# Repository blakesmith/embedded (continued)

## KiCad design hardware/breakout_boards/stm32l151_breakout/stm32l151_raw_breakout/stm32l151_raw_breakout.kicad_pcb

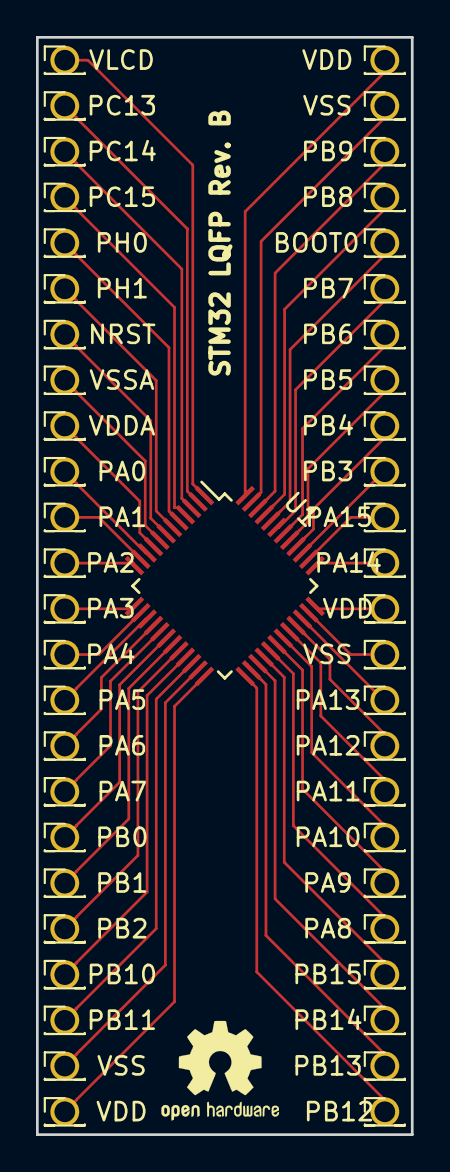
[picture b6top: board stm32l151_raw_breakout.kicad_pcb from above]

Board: 2 copper layers, 20.8 x 61.0 mm, 49 parts (0 on the bottom side), 48 nets.

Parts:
BOOT0: Conn_01x01; Pin_Header_Straight_1x01_Pitch1.27mm
NRST: Conn_01x01; Pin_Header_Straight_1x01_Pitch1.27mm
PA0, PA1, PA2, PA3, PA4, PA5, PA6, PA7, PA8, PA9, PA10, PA11, PA12, PA13, PA14, PA15: Conn_01x01; Pin_Header_Straight_1x01_Pitch1.27mm
PB0, PB1, PB2, PB3, PB4, PB5, PB6, PB7, PB8, PB9, PB10, PB11, PB12, PB13, PB14, PB15: Conn_01x01; Pin_Header_Straight_1x01_Pitch1.27mm
PC13, PC14, PC15: Conn_01x01; Pin_Header_Straight_1x01_Pitch1.27mm
PH0, PH1: Conn_01x01; Pin_Header_Straight_1x01_Pitch1.27mm
U1: STM32L151CCTx; LQFP-48_7x7mm_Pitch0.5mm
VDD: Conn_01x01; Pin_Header_Straight_1x01_Pitch1.27mm
VDD#2, VDD#3: Conn_01x01; Pin_Header_Straight_1x01_Pitch1.27mm
VDDA: Conn_01x01; Pin_Header_Straight_1x01_Pitch1.27mm
VLCD: Conn_01x01; Pin_Header_Straight_1x01_Pitch1.27mm
VSS: Conn_01x01; Pin_Header_Straight_1x01_Pitch1.27mm
VSS#2, VSS#3: Conn_01x01; Pin_Header_Straight_1x01_Pitch1.27mm
VSSA: Conn_01x01; Pin_Header_Straight_1x01_Pitch1.27mm

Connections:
unnamed: NRST.1, U1.7
unnamed: BOOT0.1, U1.44
unnamed: U1.1, VLCD.1
unnamed: PH0.1, U1.5
unnamed: PH1.1, U1.6
unnamed: PC13.1, U1.2
unnamed: PC14.1, U1.3
unnamed: PC15.1, U1.4
unnamed: PB0.1, U1.18
unnamed: PB1.1, U1.19
unnamed: PB2.1, U1.20
unnamed: PB3.1, U1.39
unnamed: PB4.1, U1.40
unnamed: PB5.1, U1.41
unnamed: PB6.1, U1.42
unnamed: PB7.1, U1.43
unnamed: PB8.1, U1.45
unnamed: PB9.1, U1.46
unnamed: PB10.1, U1.21
unnamed: PB11.1, U1.22
unnamed: PB12.1, U1.25
unnamed: PB13.1, U1.26
unnamed: PB14.1, U1.27
unnamed: PB15.1, U1.28
unnamed: U1.24, VDD.1
unnamed: U1.23, VSS.1
unnamed: U1.36, VDD#2.1
unnamed: U1.35, VSS#2.1
unnamed: U1.48, VDD#3.1
unnamed: U1.47, VSS#3.1
unnamed: U1.9, VDDA.1
unnamed: U1.8, VSSA.1
unnamed: PA0.1, U1.10
unnamed: PA1.1, U1.11
unnamed: PA2.1, U1.12
unnamed: PA3.1, U1.13
unnamed: PA4.1, U1.14
unnamed: PA5.1, U1.15
unnamed: PA6.1, U1.16
unnamed: PA7.1, U1.17
unnamed: PA8.1, U1.29
unnamed: PA9.1, U1.30
unnamed: PA10.1, U1.31
unnamed: PA11.1, U1.32
unnamed: PA12.1, U1.33
unnamed: PA13.1, U1.34
unnamed: PA14.1, U1.37
unnamed: PA15.1, U1.38

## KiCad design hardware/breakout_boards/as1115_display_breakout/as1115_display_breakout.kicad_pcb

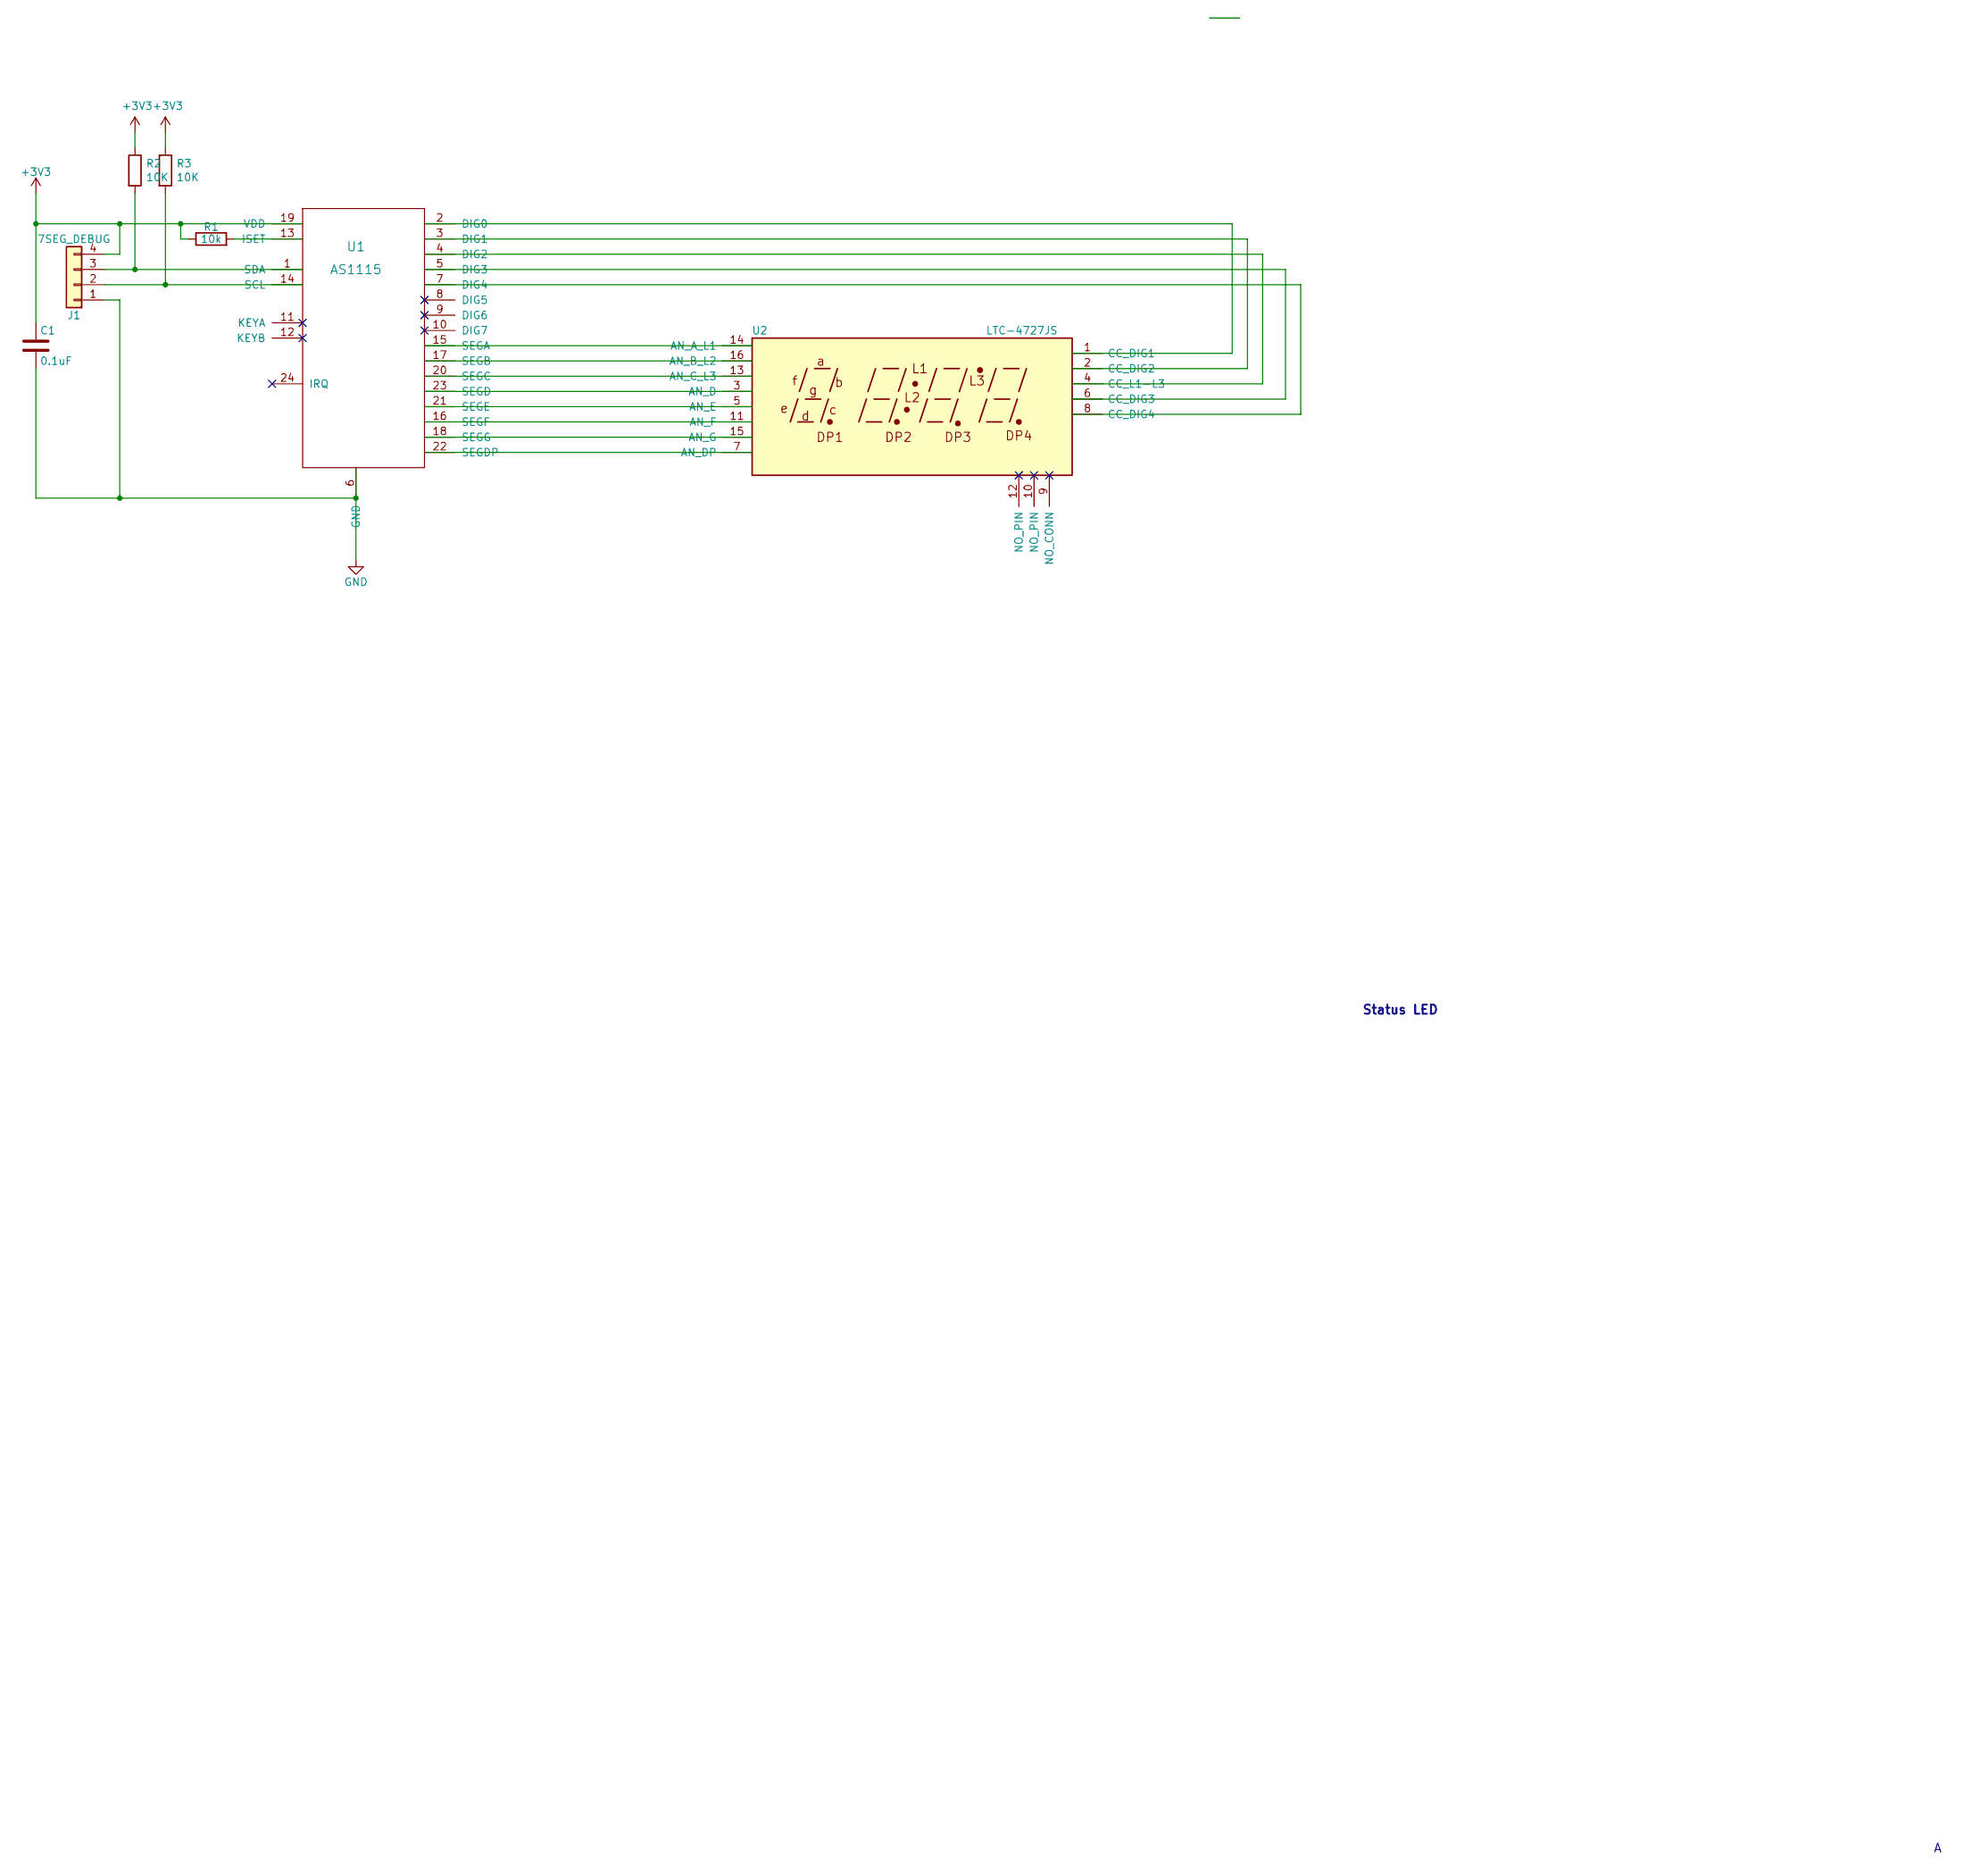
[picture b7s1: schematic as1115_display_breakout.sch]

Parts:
C1: 0.1uF; C_0805_HandSoldering
J1: 7SEG_DEBUG; Pin_Header_Straight_1x04_Pitch2.54mm
R1: 10k; R_0805_HandSoldering
R2, R3: 10K; R_0805_HandSoldering
U1: AS1115; QSOP-24_3.9x8.7mm_Pitch0.635mm
U2: LTC-4727JS; LTC-4727

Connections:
+3V3: C1.1, J1.4, R1.1, R2.1, R3.1, U1.19 (VDD)
GND: C1.2, J1.1, U1.6 (GND)
unnamed: J1.2, R3.2, U1.14 (SCL)
unnamed: J1.3, R2.2, U1.1 (SDA)
unnamed: R1.2, U1.13 (ISET)
unnamed: U1.2 (DIG0), U2.1 (CC_DIG1)
unnamed: U1.3 (DIG1), U2.2 (CC_DIG2)
unnamed: U1.4 (DIG2), U2.4 (CC_L1-L3)
unnamed: U1.5 (DIG3), U2.6 (CC_DIG3)
unnamed: U1.7 (DIG4), U2.8 (CC_DIG4)
unnamed: U1.15 (SEGA), U2.14 (AN_A_L1)
unnamed: U1.16 (SEGF), U2.11 (AN_F)
unnamed: U1.17 (SEGB), U2.16 (AN_B_L2)
unnamed: U1.18 (SEGG), U2.15 (AN_G)
unnamed: U1.20 (SEGC), U2.13 (AN_C_L3)
unnamed: U1.21 (SEGE), U2.5 (AN_E)
unnamed: U1.22 (SEGDP), U2.7 (AN_DP)
unnamed: U1.23 (SEGD), U2.3 (AN_D)

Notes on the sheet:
Status LED

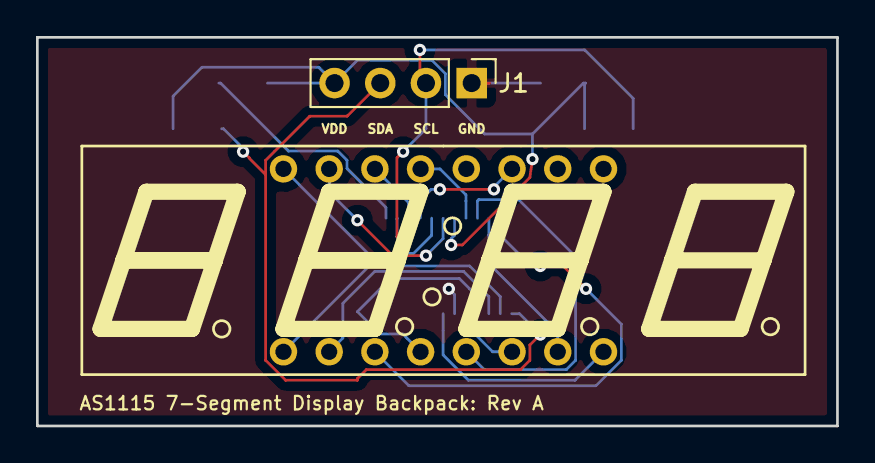
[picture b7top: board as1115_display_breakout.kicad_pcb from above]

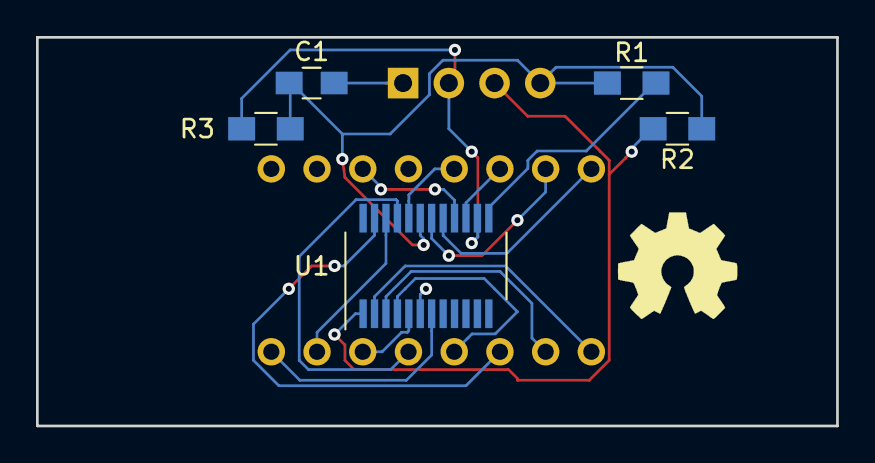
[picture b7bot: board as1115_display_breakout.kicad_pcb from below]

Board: 2 copper layers, 44.4 x 21.6 mm, 7 parts (5 on the bottom side), 18 nets.

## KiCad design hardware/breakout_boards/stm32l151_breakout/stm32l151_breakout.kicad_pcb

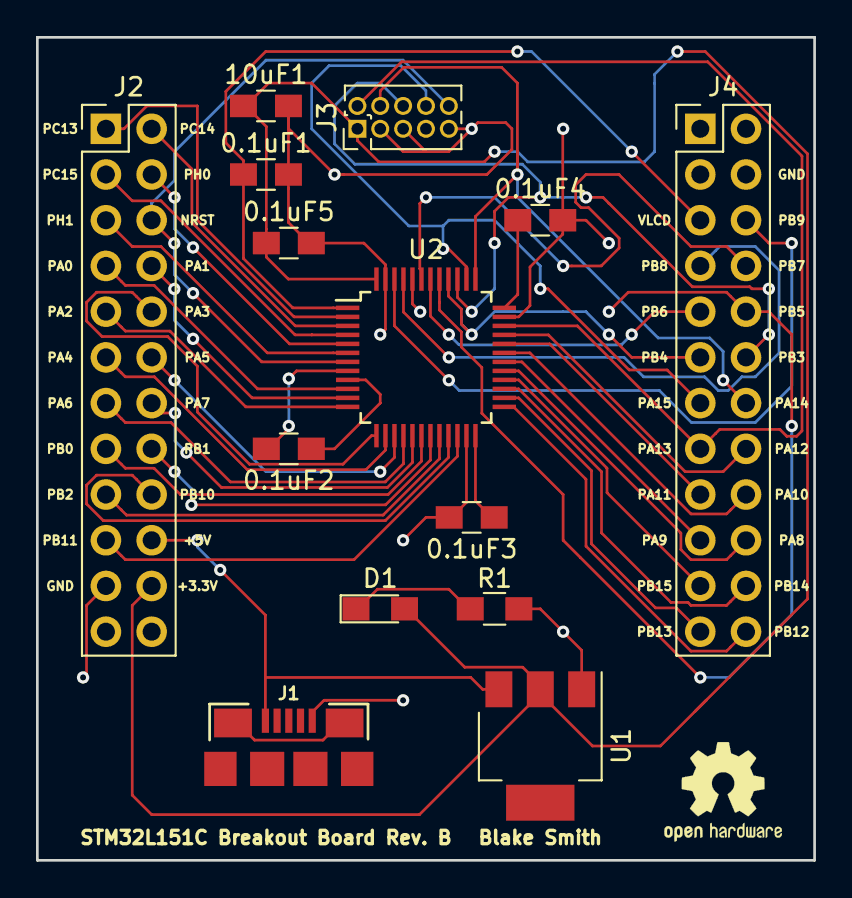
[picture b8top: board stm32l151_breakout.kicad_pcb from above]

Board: 2 copper layers, 43.2 x 45.7 mm, 14 parts (0 on the bottom side), 46 nets.

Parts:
0.1uF1: C1; C_0805_HandSoldering
0.1uF2: C2; C_0805_HandSoldering
0.1uF3: C3; C_0805_HandSoldering
0.1uF4: C4; C_0805_HandSoldering
0.1uF5: C5; C_0805_HandSoldering
10uF1: C6; C_0805_HandSoldering
D1: LED; LED_0805_HandSoldering
J1: USB_B_Micro; USB-MICRO-B-FCI-10118192
J2, J4: Conn_01x24_Male; Pin_Header_Straight_2x12_Pitch2.54mm
J3: Conn_ARM_JTAG_SWD_10; Pin_Header_Straight_2x05_Pitch1.27mm
R1: 300; R_0805_HandSoldering
U1: LD1117-3.3; SOT-223
U2: STM32L151C; LQFP-48_7x7mm_Pitch0.5mm

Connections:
/+3.3V: 0.1uF5.1, 10uF1.1, D1.2, J2.22, J3.1, U1.2, U2.48
/JTCK: J3.4, J4.14, U2.37
/JTDI: J3.8, J4.13, U2.38
/JTDO: J3.6, J4.12, U2.39
/JTMS: J3.2, J4.15, U2.34
/JTRST: J2.6, J3.10, U2.7
/VDDA: 0.1uF2.1, U2.9
/VDD_1: 0.1uF3.1, U2.24
/VDD_2: 0.1uF4.1, U2.36
/VLCD: 0.1uF1.1, J4.5, U2.1
GND: 0.1uF1.2, 0.1uF2.2, 0.1uF3.2, 0.1uF4.2, 0.1uF5.2, 10uF1.2, J1.5, J2.21, J3.3, J3.5, J3.9, J4.4, R1.2, U1.1, U2.8, U2.23, U2.35, U2.44, U2.47
unnamed: D1.1, R1.1
unnamed: J1.1, J2.20, U1.3
unnamed: J2.1, U2.2
unnamed: J2.2, U2.3
unnamed: J2.3, U2.4
unnamed: J2.4, U2.5
unnamed: J2.5, U2.6
unnamed: J2.7, U2.10
unnamed: J2.8, U2.11
unnamed: J2.9, U2.12
unnamed: J2.10, U2.13
unnamed: J2.11, U2.14
unnamed: J2.12, U2.15
unnamed: J2.13, U2.16
unnamed: J2.14, U2.17
unnamed: J2.15, U2.18
unnamed: J2.16, U2.19
unnamed: J2.17, U2.20
unnamed: J2.18, U2.21
unnamed: J2.19, U2.22
unnamed: J4.6, U2.46
unnamed: J4.7, U2.45
unnamed: J4.8, U2.43
unnamed: J4.9, U2.42
unnamed: J4.10, U2.41
unnamed: J4.11, U2.40
unnamed: J4.16, U2.33
unnamed: J4.17, U2.32
unnamed: J4.18, U2.31
unnamed: J4.19, U2.30
unnamed: J4.20, U2.29
unnamed: J4.21, U2.28
unnamed: J4.22, U2.27
unnamed: J4.23, U2.26
unnamed: J4.24, U2.25

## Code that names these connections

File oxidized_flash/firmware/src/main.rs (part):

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    pin flash_d3 = a11,

    // USB
    pin usb_dp = a25,
    pin usb_dm = a24,
);

struct Devices {
    pub ok_led: gpio::Pa20<Output<OpenDrain>>,
    pub button_switch: gpio::Pa21<Input<PullUp>>,
    pub apa102: Apa102<
        SPIMaster2<
            hal::sercom::Sercom2Pad2<gpio::Pa14<gpio::PfC>>,
            hal::sercom::Sercom2Pad0<gpio::Pa12<gpio::PfC>>,
            hal::sercom::Sercom2Pad1<gpio::Pa13<gpio::PfC>>,
        >,
    >,
    pub delay: Delay,
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        let apa_nc = pins.apa_nc.into_pull_up_input(&mut pins.port);
        let gclk0 = clocks.gclk0();
        let spi: SPIMaster2<
            hal::sercom::Sercom2Pad2<gpio::Pa14<gpio::PfC>>,
            hal::sercom::Sercom2Pad0<gpio::Pa12<gpio::PfC>>,
            hal::sercom::Sercom2Pad1<gpio::Pa13<gpio::PfC>>,
        > = SPIMaster2::new(
            &clocks.sercom2_core(&gclk0).unwrap(),
            KiloHertz(5),
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                USB_ALLOCATOR = Some(UsbBusAllocator::new(UsbBus::new(
                    usb_clock,
                    &mut peripherals.MCLK,
                    pins.usb_dm.into_function(&mut pins.port),
                    pins.usb_dp.into_function(&mut pins.port),
                    peripherals.USB,
                )));
                USB_ALLOCATOR.as_ref().unwrap()
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
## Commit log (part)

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2018-04-16 Use reusable target config values
2018-04-16 Move common stm32 binary dependencies into its own library
2018-04-16 Use shared linker scripts
2018-04-16 Use common stm32 common binary files
2018-04-16 No need for the stm32f4xx header
2018-04-16 Convert the display ocd script to a bazel generated one
2018-04-18 Support positional based whole number writing, mostly for our clock
2018-04-18 Rename n_digits_ -> n_positions_
2018-04-22 Get display updating, not correct time
2018-04-22 Make clock compile again
2018-04-22 Get clock working
2018-04-22 Make clock compile on stm32l1 again
2018-04-23 Extract out UI class
2018-04-23 Get colon toggle working again
2018-04-23 Get UI update working
2018-04-23 Break out ui actions
2018-04-24 Add stm32f4 raw breakout board
2018-04-26 Add initial clock schematic, still needs crystal oscillator
2018-04-27 Remove unused function and unused import
2018-04-29 Add initial cs43l22 breakout board
2018-04-30 Start spreading out the pcb
2018-05-07 Add breakout flash script
2018-05-21 Reset run the file as well
2018-05-22 Save stm32 raw breakout board
2018-05-22 Do correct colon measure toggling
2018-05-22 Assign clock footprints
2018-05-22 Start laying out clock footprints
2018-05-23 Connect all clock nets
2018-05-24 Add clock logo
2018-05-28 Fill out cs43l22 breakout board
2018-05-28 Update gitignore
2018-06-01 Blink the OK led every half second as well
2018-06-01 Add additional clock bill of materials
2018-06-01 Add more to gitignore
2018-06-04 Compile the usb hid class.
2018-06-04 Make keebee project. Move project specific usb files.
2018-06-04 Get a keebee binary produced.
2018-06-04 Add keebee BOM.
2018-06-04 Breakout clock interrupt handlers.
2018-06-08 Fetch subseconds, and set the correct LSE dividers for STM32L1
2018-06-08 Dynamically configure the clock source crystal
2018-06-09 Encapsulate sync and async prediv methods
2018-06-09 Move methods
2018-06-09 Scale subsecond to an 8 bit unsigned integer.
2018-06-09 Add initial stand scad drawing.
2018-06-09 Add USB cutout.
2018-06-09 Add pcb thickness tolerance.
2018-06-10 Rev B. of clock. Power rails. SMD JTAG connector.
2018-06-10 Minor track cleanup.
2018-06-10 Move Rev. B text.
2018-06-10 Swap out 10-pin JTAG header.
2018-06-10 Adjust BOM before rev. B order.
2018-06-17 Enable the external oscillator, fix pinout.
2018-06-17 Require a display refresh when flipping to the next second.
2018-06-17 For now, toggle error
2018-06-17 Move AS1115 decoupling cap.
2018-06-17 Toggle both LEDs in an alternating fashion.
2018-06-17 Support the correct number of set positions.
2018-06-21 Add initial scad keyboard drawing, with MX datasheet.
2018-06-21 Calculate the plate width based on the switch dimensions.
2018-06-23 Make the plate 2D, and add rounded corners.
2018-06-23 Correct pitch centering, without edge padding.
2018-06-23 Re-align key cutout rounded hulls, fix radius. Pass key size through.
2018-06-23 Refactor row switch cutouts.
2018-06-24 Add more clock tolerances.
2018-06-24 Add small space bar stabilizer.
2018-06-24 Remove unused code.
2018-06-24 Add mounting holes
2018-06-24 Align stabilizer squares correctly.
2018-06-24 Make row 0 zero based.
2018-06-24 Add initial key labels.
2018-06-24 Add dsa_keycap model.
2018-06-24 Add switches
2018-06-24 Move key labels to keycaps
2018-06-24 Move around arrow keys
2018-06-24 Change key label colors
2018-06-25 Add stm32f042k6 data sheet
2018-06-25 Add in keebee power schematic
2018-06-26 Add key matrix sub-sheet
2018-06-26 Actually add the sub-sheet.
2018-06-26 Add top plate dimension echoing.
2018-06-27 Add diode to bom.
2018-06-27 Add diodes to the key matrix
2018-06-27 Add Diode footprints
2018-06-27 Add layout switch.
2018-06-28 Remove unused activity status LED.
2018-06-28 Add status LED, layout dip switch and reset switch.
2018-06-28 Fill in remaining BOM
2018-06-28 Add TODO list
2018-06-28 Add more prototype items to order
2018-06-29 Rearrange RTC startup order.
2018-06-29 Allow status led tick to be enabled and disabled.
2018-06-29 Add stabilizer kit to BOM.
2018-06-30 Add boot selection switch.
2018-07-01 Always switch the status LEDs on each half-tick.
2018-07-08 No need for extra formatting.
2018-07-09 Make gpio interfaces work with the stm32 hal drivers.
2018-07-09 Rename stm32f0 target -> stm32f042
2018-07-09 Add scan matrix to keebee.
2018-07-09 Implement full matrix scan.
2018-07-09 Implement basic scanning and status output in main.
2018-07-12 Add initial USBKeyboard class.
2018-07-12 Stub out usb initialization.
2018-07-12 Add simple human HID device descriptions.
2018-07-12 Add serial string.
2018-07-12 Add device descriptor.
2018-07-13 Do HAL_Init on startup.
2018-07-14 Correct Set / Reset of GPIO Pin.
2018-07-15 Add keebee board flash for nucleo.
2018-07-15 Single dimension arre, correct OpenDrain settings. Multi-key reading works.
2018-07-15 Move StatusLEDs off USB pins.
2018-07-16 Set GPIO pin using BSRRH and BSRRL for stm32l
2018-07-16 STM32F uses high / low BSRR GPIO registers as well
2018-07-17 Add openocd board flash
2018-07-17 Integrate keyboard into main, and trim out debug logging to slim down binary size.
2018-07-19 Get USB device to start, but fail to communicate.
2018-07-20 Send the correct USB keyboard hid description, and align the report buffer.
2018-07-20 Map keyboard buttons into hid report.
2018-07-20 Set zeros for null reports, and add modifiers as well.
2018-07-20 Add untested default key layout, and send the whole key scan.
2018-07-22 Make report buffer copying a member function.
2018-07-22 Move HIDReport.Reset into cc file.
2018-07-22 Add more key scan codes and a preliminary dvorak layout.
2018-07-23 Map modifiers into the HID report.
2018-07-23 Key should be 16 bits.
2018-07-23 Add layer switching.
2018-07-23 Support layer combinations.
2018-07-23 Extract key pipeline into its own file.
2018-07-23 Only send the report if the buffer fill operation returns 0.
2018-07-25 Fill in untested dip switch init and read.
2018-07-25 Add in dip switch setting.
2018-07-25 Add secondary test layout
2018-07-26 Add dip switch footprint, and update BOM.
2018-07-26 Assign B3F footprint to the reset switch.
2018-07-26 Add initial kicad_pcb file.
2018-07-26 Fixup imported footprint errors.
2018-07-26 Place all switches.
2018-07-26 Roughly place all footprints.
2018-07-27 Route rows and columns from scan matrix.
2018-07-27 Route some more MCU pins.
2018-07-29 Finish routing all nets.
2018-07-29 Add bottom plate, with component cutouts.
2018-07-29 Refill zones.
2018-08-02 Add in antennae and name.
2018-08-02 Add logo to PCB.
2018-08-02 Add mounting holes, and update logo.
2018-08-02 Update TODO and add bom items.
2018-08-03 Lessen 1u pitch tolerance.
2018-08-03 Fix mounting hole track clearance.
2018-08-03 Move Keebee logo to the back.
2018-08-03 Add 3d shots
2018-08-07 Check in printed top plate DXF
2018-08-10 Get keebee prototype flashing.
2018-08-10 Set correct prototype pinout, remove dip switch.
2018-08-16 Remove extraneous SYMBOL_TABLE for ht16k33 display
2018-08-18 Add address and data pin connections for RAM.
2018-08-18 Finish wiring RAM.
2018-08-19 Add display to BOM.
2018-08-21 Add led driver.
2018-08-23 Add QWERTY layout.
2018-08-25 Add a switch layout keymap.
2018-08-26 Wire in 1.69 OLED display to the schematic.
2018-08-30 Add 8MHZ crystal oscillator.
2018-08-30 Wire in flash serial IC.
2018-09-02 Replace Beat with AudioPipeline class.
2018-09-02 Add Ui and X11Display stubs.
2018-09-02 Start managing the lifecycle of some X11 objects.
2018-09-02 Quit the application on a button press.
2018-09-02 const -> constexpr
2018-09-02 Add extra shutdown log line.
2018-09-02 Remove old constexpressions.
2018-09-03 Add envelope trigger on key press.
2018-09-03 Add simple note implementation.
2018-09-03 Lookup notes by index.
2018-09-03 Remove ToString note method.
2018-09-03 Make note down input event.
2018-09-03 Move synth primitives to their own library.
2018-09-03 Add logging preprocessor function.
2018-09-09 Rely on modulo power of two unsigned integer overflow behavior of the oscillator. No need to set mixer input on note trigger.
2018-09-09 Set starting freq to 0, play with levels.
2018-09-15 First prototype working, bad latency
2018-09-15 Fix arrow key placement
2018-09-15 Make qwerty the default layout, because of software keyboard mappings.
2018-09-16 Add page up and page down keys to function layer.
2018-09-16 Make nearby buttons space bars, for left handed comfort.
2018-09-17 Integrate voice class into the audio pipeline
2018-09-17 Make oscillator mix levels even
2018-09-17 Mix down active voices to prevent clipping
2018-09-17 Rename voice choir to voice group
2018-09-18 Device description, set to detect from HID interface
2018-09-22 Implement InputEvent equality.
2018-09-22 Add NOTE_UP input event type.
2018-09-22 Listen for KeyRelease event as well
2018-09-22 Disable auto key repeat
2019-01-17 Add initial oxidized_flash bom
2019-01-18 Add ATSAMD51 data sheet
2019-01-19 Add eMMC card
2019-01-19 Check in misc kicad files
2019-01-19 Add FBGA-153 footprint
2019-01-19 Add APA102 data sheet
2019-01-19 Initial schematic eMMC connection
2019-01-25 Cleanup schematic before battery power work
2019-01-26 Assign footprints to some of the schematic
2019-01-27 Add initial schematic, and SWD interface
2019-01-27 Remove crystal
2019-01-27 Add power LED
2019-01-27 Don't tie 3.3v directly to GND
2019-01-27 Get passives close to their counterparts
2019-10-11 More routing
2019-10-11 Connect APA lights together
2019-10-20 Add SPI pins for controlling the LEDs
2019-10-27 Add in RTC and more power management
2019-10-27 Check in CAD enclosure
2019-11-02 Fill out remaining footprint assignments
2019-11-02 Fill out more BOM items
2019-11-02 Initial major component PCB layout
2019-11-02 Use side-angled SMT JST battery connector
2019-11-02 Add initial AS102 tracks
2019-12-22 Add 512M SPI flash
2019-12-22 Fixup decoupling capacitors on the SAMD
2019-12-23 Add empty firmware
2019-12-23 Make the OK LED blink
2019-12-26 Add appropriate linker settings
2019-12-26 Add release build target
2019-12-28 Update APA and flash footprints
2019-12-28 Remove 10k pullup on SWD_IO
2019-12-28 Add reset pin to SWD header
2019-12-31 Update C5 to use a hand-soldered footprint
2019-12-31 Don't couple power rail to the JTAG connector
2020-01-12 Initial working board and firmware
2020-01-15 Hack out SPI setup
2020-01-15 Get dotstar LEDs working. Need to figure out why the colors are off
2020-01-15 Only write out dotstar LEDs on button push
2020-01-19 Separate device setup from main
2020-01-19 Add initial vendored QSPI interface
2020-01-21 read_id seems to be working sometimes
2020-01-21 Set the OK led if able to read id from flash
2020-01-21 Add additional response check
2020-01-23 Halt on initial button press
2020-01-23 Rename to wait_ready
2020-01-26 Use correct pixel type ordering
2020-01-28 Some initial USB device setup
2020-01-30 Stub out initial USB keyboard setup
2020-01-31 Setup interrupts and polling behavior
2020-02-02 Get USB device with keyboard to register cleanly
2020-02-02 No need to check dfll before proceeding
2020-02-05 Get basic keys sending
2020-02-06 Fixup timings, and support multiple hid report types
2020-02-08 Send correct HID report length, and get media keys working correctly
2020-02-08 Get correct double buffer hid state change working
2020-02-08 Fix off-by-one error in add_key
2020-02-08 Consolidate into a single key enum
2020-02-11 Get a basic timer working to blink an LED
2022-06-06 Bump rgb from 0.8.16 to 0.8.32 in /oxidized_flash/firmware
    Bumps [rgb](https://github.com/kornelski/rust-rgb) from 0.8.16 to 0.8.32.
    - [Release notes](https://github.com/kornelski/rust-rgb/releases)
    - [Commits](https://github.com/kornelski/rust-rgb/commits)
    ---
    updated-dependencies:
    - dependency-name: rgb
